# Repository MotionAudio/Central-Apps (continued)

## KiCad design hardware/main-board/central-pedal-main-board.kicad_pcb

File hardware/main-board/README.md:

# Central Pedal main board - rev A

> **Superseded by rev B** (`../main-board-rev-b/`). Do not build rev A as it is: its Pi header frame (pin numbering, mounting holes,
> ribbon slot) was laid out for a mirrored Pi, which was corrected on rev B. Kept for reference only.

270 x 160 mm, 4 layers (signal / GND / 5V1 + VBAT island / signal), 1.6 mm, 1 oz, HASL or ENIG, blue or black.
Stacks behind the Raspberry Pi 4 (2x20 stacking header on the back) with the Raspberry Pi Touch Display 2 in front.
Wiring and pin map: `../../docs/MAIN-BOARD.md`. Full spec: the "Central Pedal Main Board - Design & Manufacturing Spec" doc.

## Ordering (JLCPCB / PCBWay)

Upload from `fab/`:

| File | What |
| --- | --- |
| `central-pedal-main-board-gerbers.zip` | Gerbers + Excellon drills (board edge included) |
| `central-pedal-main-board-bom-jlcpcb.csv` | BOM, with LCSC numbers where a stock part exists |
| `central-pedal-main-board-cpl-jlcpcb.csv` | Pick-and-place (top side only is populated) |
| `central-pedal-main-board-top.pdf` / `-bottom.pdf` | Assembly drawings |
| `central-pedal-main-board-netlist.txt` | Every net and the pins on it, for review |
| `not-fitted.txt` | DNP parts (gain / option jumpers) |
| `drc-report.txt` | KiCad DRC: 0 errors, 0 unconnected; warnings are silkscreen and thermal-relief notes |

Settings to pick: 4 layers, stack-up JLC04161H-7628 (or the fab's standard 4-layer), min track/space 0.15 mm, min
via 0.45 / 0.2 mm (via-in-pad on some ground pads - ask for "filled and capped" vias or accept plain), 5 boards.
Parts without an LCSC number (Neutrik jacks, pots, faders, JST connectors, the push-knobs) can be assembled by the
fab from their global sourcing or soldered by hand; the SMD side is what matters for assembly.

The CPL rotations follow KiCad's convention; the fab's review will rotate polarised parts (diodes, ICs, electrolytics)
to match the Gerbers - confirm them on the assembly preview before paying.

## Regenerating

`design.py` is the whole design (every part, pin and net). On a machine with KiCad 7 and Java:

```
python3 build.py            # place parts, planes, outline -> out/central-pedal-main-board.kicad_pcb
python3 fanout.py --pre     # plane-pad vias before routing
./pipeline.sh               # Freerouting (two passes) + fan-out + stitching
python3 maze.py             # finish any connection the router left open
python3 export.py           # -> out/fab/
```

`central-pedal-main-board.kicad_pcb` / `.kicad_pro` here are the exact routed board the rev A fab files came from.

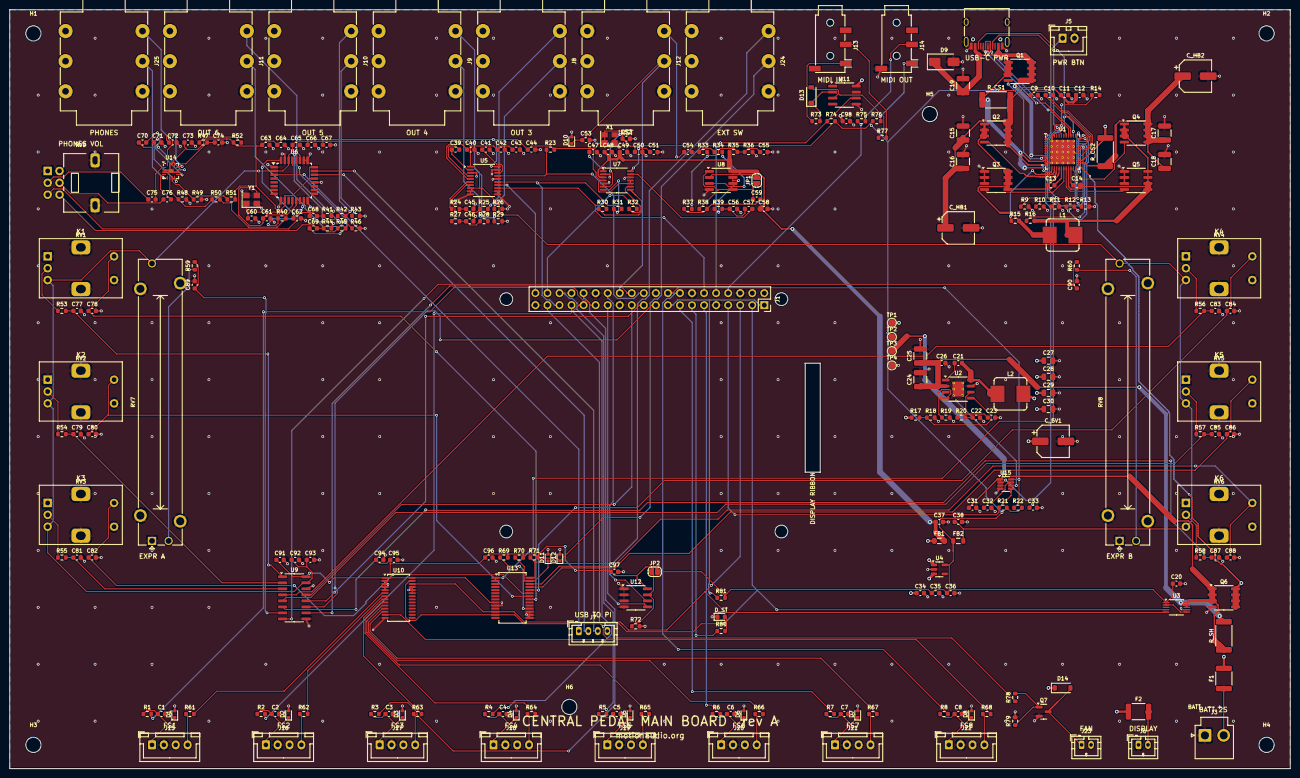
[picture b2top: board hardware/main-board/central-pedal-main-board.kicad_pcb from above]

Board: 4 copper layers, 270.0 x 160.0 mm, 279 parts (0 on the bottom side), 190 nets.

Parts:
C1, C2, C3, C4, C5, C6, C7, C8, C11, C13, C14, C20, C21, C26, C33, C42, C44, C48, C50, C52, C53, C54, C58, C63, C65, C67, C77, C78, C79, C80, C81, C82, C83, C84, C85, C86, C87, C88, C89, C90, C91, C92, C94, C96, C97, C98: 100n; C_0603_1608Metric
C9, C10, C39, C40, C41, C72: 2.2u; C_0603_1608Metric
C12, C31, C34, C35, C51, C57, C70, C71, C73, C75, C76: 1u; C_0603_1608Metric
C15, C16, C17, C18: 22u; C_1210_3225Metric
C19, C24, C25: 10u; C_1210_3225Metric
C22: 4.7n; C_0603_1608Metric
C23: 68p; C_0603_1608Metric
C27, C28, C29, C30: 22u; C_0805_2012Metric
C32: 1.5u; C_0603_1608Metric
C36, C37, C38, C43, C47, C49, C55, C62, C64, C66, C68, C69, C74, C93, C95: 10u; C_0603_1608Metric
C45, C46: 2.2n; C_0603_1608Metric
C56: 1n; C_0603_1608Metric
C59: 100p; C_0603_1608Metric
C60, C61: 22p; C_0603_1608Metric
C_5V1: 100u 10V; CP_Elec_6.3x5.8
C_HB1, C_HB2: 100u 35V; CP_Elec_6.3x5.8
D1, D2, D3, D4, D5, D6, D7, D8, D10, D11, D12: PESD5V0S1UB; D_SOD-523
D9: SMAJ24A; D_SMA
D13, D14: 1N4148W; D_SOD-123
D_ST: GREEN; LED_0603_1608Metric
F1: 7.5A; Fuse_1812_4532Metric
F2: 2A PTC; Fuse_1812_4532Metric
FB1, FB2: FB 600R; L_0805_2012Metric
H1, H2, H3, H4, H5, H6: M3; MountingHole_3.2mm_M3
HPI1, HPI2, HPI3, HPI4: MountingHole_2.7mm
J1: RASPBERRY PI 4; PinSocket_2x20_P2.54mm_Vertical
J2: USB-C; USB_C_Receptacle_HRO_TYPE-C-31-M-12
J3: BATTERY 2S; JST_VH_B2P-VH_1x02_P3.96mm_Vertical
J5: POWER BTN; JST_XH_B2B-XH-A_1x02_P2.50mm_Vertical
J6: DISPLAY 5V; JST_PH_B2B-PH-K_1x02_P2.00mm_Vertical
J7: USB TO PI; JST_PH_B4B-PH-K_1x04_P2.00mm_Vertical
J8, J9, J10, J11, J12, J24, J25: 1/4in TRS; Jack_6.35mm_Neutrik_NMJ6HCD2_Horizontal
J13: MIDI IN; Jack_3.5mm_PJ320D_Horizontal
J14: MIDI OUT; Jack_3.5mm_PJ320D_Horizontal
J15: FOOTSW 1; JST_XH_B4B-XH-A_1x04_P2.50mm_Vertical
J16: FOOTSW 2; JST_XH_B4B-XH-A_1x04_P2.50mm_Vertical
J17: FOOTSW 3; JST_XH_B4B-XH-A_1x04_P2.50mm_Vertical
J18: FOOTSW 4; JST_XH_B4B-XH-A_1x04_P2.50mm_Vertical
J19: FOOTSW 5; JST_XH_B4B-XH-A_1x04_P2.50mm_Vertical
J20: FOOTSW 6; JST_XH_B4B-XH-A_1x04_P2.50mm_Vertical
J21: FOOTSW 7; JST_XH_B4B-XH-A_1x04_P2.50mm_Vertical
J22: FOOTSW 8; JST_XH_B4B-XH-A_1x04_P2.50mm_Vertical
J23: FAN; JST_PH_B2B-PH-K_1x02_P2.00mm_Vertical
JP1: GAIN 0dB; SolderJumper-2_P1.3mm_Open_RoundedPad1.0x1.5mm
JP2: EEPROM WP; SolderJumper-2_P1.3mm_Open_RoundedPad1.0x1.5mm
L1: 10uH 6A; L_Bourns_SRP7028A_7.3x6.6mm
L2: 4.7uH 9A; L_Bourns_SRP7028A_7.3x6.6mm
Q1, Q2, Q3, Q4, Q5: AO4406A; SOIC-8_3.9x4.9mm_P1.27mm
Q6: AO4407A; SOIC-8_3.9x4.9mm_P1.27mm
Q7: AO3400A; SOT-23
R1, R2, R3, R4, R5, R6, R7, R8, R25, R26, R28, R29, R34, R42, R43, R45, R46, R78: 100R; R_0603_1608Metric
R9: 6.2k; R_0603_1608Metric
R10, R11, R12, R13, R14, R18, R37, R40, R69, R70, R71, R72, R79: 10k; R_0603_1608Metric
R15, R16, R75: 10R; R_0603_1608Metric
R17: 53.6k; R_0603_1608Metric
R19: 162k; R_0603_1608Metric
R20: 16.9k; R_0603_1608Metric
R21, R23, R35, R36, R47: 100k; R_0603_1608Metric
R22, R39: 4.7k; R_0603_1608Metric
R24, R27: 470R; R_0603_1608Metric
R30, R31, R32, R76: 33R; R_0603_1608Metric
R33: 1M; R_0603_1608Metric
R38: 30k; R_0603_1608Metric
R41, R44: 47k; R_0603_1608Metric
R48, R49, R50, R51, R52, R77, R81: 0R; R_0603_1608Metric
R53, R54, R55, R56, R57, R58, R59, R60, R80: 1k; R_0603_1608Metric
R61, R62, R63, R64, R65, R66, R67, R68: 330R; R_0603_1608Metric
R73: 220R; R_0603_1608Metric
R74: 2.2k; R_0603_1608Metric
RV1, RV2, RV3, RV4, RV5, RV6: B10K push; RV09_Push_Vertical
RV7, RV8: 10k lin slide; Potentiometer_Bourns_PTA4543_Single_Slide
RV9: A10K dual; Potentiometer_Alps_RK09L_Double_Vertical
R_CS1, R_CS2: 5mR; R_2512_6332Metric
R_SH: 5mR; R_2512_6332Metric
TP1: 5V1; TestPoint_Pad_D1.5mm
TP2: 3V3; TestPoint_Pad_D1.5mm
TP3: VBAT; TestPoint_Pad_D1.5mm
TP4: GND; TestPoint_Pad_D1.5mm
U1: IP2368_BZ; QFN-48-1EP_7x7mm_P0.5mm_EP5.15x5.15mm_ThermalVias
U2: TPS54560DDAR; HSOP-8-1EP_3.9x4.9mm_P1.27mm_EP2.41x3.1mm_ThermalVias
U3: INA226AIDGSR; VSSOP-10_3x3mm_P0.5mm
U4: TLV75533PDBVR; SOT-23-5
U5: PCM5102APWR; TSSOP-20_4.4x6.5mm_P0.65mm
U6: PCM2706CPJTR; TQFP-32_7x7mm_P0.8mm
U7: PCM1808PWR; TSSOP-14_4.4x5mm_P0.65mm
U8: OPA1678IDR; SOIC-8_3.9x4.9mm_P1.27mm
U9: MCP3208-CI/SL; SOIC-16_3.9x9.9mm_P1.27mm
U10: PCA9685PW; TSSOP-28_4.4x9.7mm_P0.65mm
U11: 6N138S; SOIC-8_3.9x4.9mm_P1.27mm
U12: CAT24C32WI-GT3; SOIC-8_3.9x4.9mm_P1.27mm
U13: MCP23017-E/SS; SSOP-28_5.3x10.2mm_P0.65mm
U14: TPA6132A2RTER; Texas_RTE_WQFN-16-1EP_3x3mm_P0.5mm_EP1.2x0.8mm_ThermalVias
U15: LTC2954CTS8-1; TSOT-23-8
X1: 12.288MHz; Oscillator_SMD_Abracon_ASE-4Pin_3.2x2.5mm
Y1: 12MHz; Crystal_SMD_3225-4Pin_3.2x2.5mm

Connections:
3V3: C20.1, C35.1, C36.1, C44.1, C50.1, C52.1, C63.1, C64.1, C73.1, C91.1, C94.1, C95.1, C96.1, C97.1, FB2.1, JP2.2, R14.2, R21.2, R22.2, R23.2, R40.2, R50.2, R51.2, R52.1, R69.2, R70.2, R71.2, R74.2, R76.1, R81.2, TP2.1, U3.1, U3.2, U3.6, U4.5, U5.20, U6.10, U6.21, U6.24, U7.4, U7.10, U7.11, U9.16, U10.1, U10.28, U12.8, U13.9, U14.14, X1.1, X1.4
3V3A: C38.1, C42.1, C43.1, C65.1, C66.1, C67.1, C92.1, C93.1, FB2.2, RV1.3, RV2.3, RV3.3, RV4.3, RV5.3, RV6.3, RV7.3, RV8.3, U5.1, U5.8, U6.2, U6.27, U6.30, U9.15
5V1: C27.1, C28.1, C29.1, C30.1, C34.1, C98.1, C_5V1.1, D14.1, F2.1, FB1.1, J1.2, J1.4, J15.3, J16.3, J17.3, J18.3, J19.3, J20.3, J21.3, J22.3, J23.2, L2.2, R17.1, TP1.1, U4.1, U4.3, U11.8
5VA: C37.1, C48.1, C49.1, C58.1, FB1.2, R35.1, U7.3, U8.8
ADC_BCK: R30.1, U7.8
ADC_CH0: C77.1, R53.2, U9.1
ADC_CH1: C79.1, R54.2, U9.2
ADC_CH2: C81.1, R55.2, U9.3
ADC_CH3: C83.1, R56.2, U9.4
ADC_CH4: C85.1, R57.2, U9.5
ADC_CH5: C87.1, R58.2, U9.6
ADC_CH6: C89.1, R59.2, U9.7
ADC_CH7: C90.1, R60.2, U9.8
ADC_DOUT: R32.1, U7.9
ADC_INL: C57.2, U7.13
ADC_INR: C51.1, U7.14
ADC_LRCK: R31.1, U7.7
ADC_RC: C56.1, C57.1, R39.2
ADC_SCK: U7.6, X1.3
ADC_VREF: C47.1, U7.1
BAT_RAW: F1.1, J3.2
BOOT: C21.1, U2.1
BST1: C13.1, U1.17
BST2: C14.1, U1.22
CAPM: C39.2, U5.4
CAPP: C39.1, U5.2
CC1: J2.A5, U1.41
CC2: J2.B5, U1.38
CHG_LED1: R14.1, U1.43, U13.1
COMP: C23.1, R20.1, U2.6
COMP_C: C22.1, R20.2
CPN: C70.2, U14.9
CPP: C70.1, U14.11
DAC1_L: R24.1, U5.6
DAC1_R: R27.1, U5.7
DAC2_L: C68.1, U6.28
DAC2_R: C69.1, U6.29
DAC_XSMT: J1.22, R23.1, U5.17
DISP_5V: F2.2, J6.2
EEP_WP: JP2.1, R72.1, U12.7
EN_5V: U2.3, U15.6
EXP_RST: R69.1, U13.18
EXT_A: D11.1, J24.T, R70.1, U13.27
EXT_B: D12.1, J24.R, R71.1, U13.28
F1_L: C45.1, R24.2, R25.1
F1_R: C46.1, R27.2, R28.1
FADER1_W: R59.1, RV7.2
FADER2_W: R60.1, RV8.2
FAN_CTL: J1.37, R78.1
FAN_G: Q7.1, R78.2, R79.1
FAN_N: D14.2, J23.1, Q7.3
FB: R17.2, R18.1, U2.5
FS1: C1.1, D1.1, J15.1, R1.1
FS2: C2.1, D2.1, J16.1, R2.1
FS3: C3.1, D3.1, J17.1, R3.1
FS4: C4.1, D4.1, J18.1, R4.1
FS5: C5.1, D5.1, J19.1, R5.1
FS6: C6.1, D6.1, J20.1, R6.1
FS7: C7.1, D7.1, J21.1, R7.1
FS8: C8.1, D8.1, J22.1, R8.1
GND: C1.2, C2.2, C3.2, C4.2, C5.2, C6.2, C7.2, C8.2, C9.2, C10.2, C11.2, C12.2, C15.2, C16.2, C17.2, C18.2, C19.2, C20.2, C22.2, C23.2, C24.2, C25.2, C26.2, C27.2, C28.2, C29.2, C30.2, C31.2, C32.2, C33.2, C34.2, C35.2, C36.2, C37.2, C38.2, C40.2, C41.2, C42.2, C43.2, C44.2, C45.2, C46.2, C47.2, C48.2, C49.2, C50.2, C51.2, C52.2, C53.2, C55.2, C56.2, C58.2, C60.2, C61.2, C62.2, C63.2, C64.2, C65.2, C66.2, C67.2, C71.2, C72.2, C73.2, C74.2, C77.2, C78.2, C79.2, C80.2, C81.2, C82.2, C83.2, C84.2, C85.2, C86.2, C87.2, C88.2, C89.2, C90.2, C91.2, C92.2, C93.2, C94.2, C95.2, C96.2, C97.2, C98.2, C_5V1.2, C_HB1.2, C_HB2.2, D1.2, D2.2, D3.2, D4.2, D5.2, D6.2, D7.2, D8.2, D9.2, D10.2, D11.2, D12.2, D_ST.1, J1.6, J1.9, J1.14, J1.20, J1.25, J1.30, J1.34, J1.39, J2.A1, J2.A12, J2.B1, J2.B12, J2.S1, J3.1, J5.2, J6.1, J7.4, J8.S, J9.S, J10.S, J11.S, J12.S, J12.TN, J14.S, J15.2, J16.2, J17.2, J18.2, J19.2, J20.2, J21.2, J22.2, J24.S, J25.S, Q3.1, Q3.2, Q3.3, Q5.1, Q5.2, Q5.3, Q6.4, Q7.2, R9.2, R10.2, R11.2, R12.2, R13.2, R18.2, R19.2, R26.2, R29.2, R36.2, R41.2, R43.2, R44.2, R46.2, R48.2, R49.2, R72.2, R79.2, RV1.1, RV1.MP, RV1.S2, RV2.1, RV2.MP, RV2.S2, RV3.1, RV3.MP, RV3.S2, RV4.1, RV4.MP, RV4.S2, RV5.1, RV5.MP, RV5.S2, RV6.1, RV6.MP, RV6.S2, RV7.1, RV7.MP, RV8.1, RV8.MP, RV9.1, RV9.4, RV9.MP, TP4.1, U1.11, U1.30, U1.47, U1.49, U2.7, U2.9, U3.7, U4.2, U5.3, U5.9, U5.10, U5.11, U5.12, U5.16, U5.19, U6.1, U6.9, U6.16, U6.20, U6.25, U6.26, U6.31, U7.2, U7.5, U7.12, U8.4, U9.9, U9.14, U10.2, U10.3, U10.4, U10.5, U10.14, U10.23, U10.24, U10.25, U11.5, U12.1, U12.2, U12.3, U12.4, U13.10, U13.15, U13.16, U13.17, U14.2, U14.3, U14.10, U14.15, U14.17, U15.4, X1.2, Y1.2, Y1.4
GND_R3: J8.R, R26.1
GND_R4: J9.R, R29.1
GND_R5: J10.R, R43.1
GND_R6: J11.R, R46.1
GPIO_FS1: J1.29, R1.2
GPIO_FS2: J1.31, R2.2
GPIO_FS3: J1.32, R3.2
GPIO_FS4: J1.33, R4.2
GPIO_FS5: J1.36, R5.2
GPIO_FS6: J1.11, R6.2
GPIO_FS7: J1.15, R7.2
GPIO_FS8: J1.16, R8.2
HB_OUT: C17.1, C18.1, C_HB2.1, Q4.5, Q4.6, Q4.7, Q4.8, R_CS2.1, U1.26
HG1: Q2.4, U1.16
HG2: Q4.4, U1.23
HPIN_L: C75.2, U14.1
HPIN_R: C76.2, U14.4
HPVDD: C72.1, U14.12
HPVOL_L: C75.1, RV9.2
HPVOL_R: C76.1, RV9.5
HPVSS: C71.1, U14.8
HP_EN: C74.1, R47.2, U14.13
HP_G0: R48.1, R50.1, U14.6
HP_G1: R49.1, R51.1, U14.7
HP_L: J25.T, U14.16
HP_R: J25.R, U14.5
I2S_BCK: J1.12, R30.2, U5.13
I2S_DIN: J1.38, R32.2
I2S_DOUT: J1.40, U5.14
I2S_LRCK: J1.35, R31.2, U5.15
ID_SC: J1.28, U12.6
ID_SD: J1.27, U12.5
INST_DET: C53.1, D10.1, J1.26, J12.R
INST_IN: C54.1, J12.T
IN_AC: C54.2, R33.1, R34.1
KCLK1: C78.1, RV1.S1, U13.21
KCLK2: C80.1, RV2.S1, U13.22
KCLK3: C82.1, RV3.S1, U13.23
KCLK4: C84.1, RV4.S1, U13.24
KCLK5: C86.1, RV5.S1, U13.25
KCLK6: C88.1, RV6.S1, U13.26
KNOB1_W: R53.1, RV1.2
KNOB2_W: R54.1, RV2.2
KNOB3_W: R55.1, RV3.2
KNOB4_W: R56.1, RV4.2
KNOB5_W: R57.1, RV5.2
KNOB6_W: R58.1, RV6.2
LDOO: C41.1, U5.18
LED1: R61.2, U10.6
LED2: R62.2, U10.7
LED3: R63.2, U10.8
LED4: R64.2, U10.9
LED5: R65.2, U10.10
LED6: R66.2, U10.11
LED7: R67.2, U10.12
LED8: R68.2, U10.13
LEDK1: J15.4, R61.1
LEDK2: J16.4, R62.1
LEDK3: J17.4, R63.1
LEDK4: J18.4, R64.1
LEDK5: J19.4, R65.1
LEDK6: J20.4, R66.1
LEDK7: J21.4, R67.1
LEDK8: J22.4, R68.1
LED_ST_A: D_ST.2, R80.2
LG1: Q3.4, U1.19
LG2: Q5.4, U1.20
LINE_L: C68.2, R41.1, R42.1, RV9.3
LINE_R: C69.2, R44.1, R45.1, RV9.6
LX1: C13.2, L1.1, Q2.1, Q2.2, Q2.3, Q3.5, Q3.6, Q3.7, Q3.8, R15.2, U1.18
LX2: C14.2, L1.2, Q4.1, Q4.2, Q4.3, Q5.5, Q5.6, Q5.7, Q5.8, R16.2, U1.21
MIDI_A: D13.1, R73.2, U11.2
MIDI_IN_R: J13.R1, R77.2
MIDI_IN_T: J13.T, R73.1
MIDI_K: D13.2, R77.1, U11.3
MIDI_OUT_R: J14.R1, R75.2
MIDI_OUT_T: J14.T, R76.2
MIDI_RX: J1.10, R74.1, U11.6
MIDI_TX: J1.8, R75.1
OUT3: J8.T, R25.2
OUT4: J9.T, R28.2
OUT5: J10.T, R42.2
OUT6: J11.T, R45.2
PB: C33.1, J5.1, U15.2
PCIN: R15.1, U1.15
PCON: R16.1, U1.24
PDT: C32.1, U15.7
PG_5V: R47.1, R52.2
PI_3V3: J1.1, J1.17, R81.1
PRE_A: C59.1, JP1.1, R38.1, U8.1, U8.5
PRE_AN: C59.2, JP1.2, R37.1, R38.2, U8.2
PRE_AP: R34.2, U8.3
PRE_B: R39.1, U8.6, U8.7
PWR_INT: J1.7, R21.1, U15.5
PWR_KILL: J1.18, R22.1, U15.8
ROM_DT: R40.1, U6.15
RT: R19.1, U2.4
R_BATNUM: R9.1, U1.33
R_FCAP: R10.1, U1.34
R_ISET: R12.1, U1.36
R_NTC: R13.1, U1.37
R_VSET: R11.1, U1.35
SCL: J1.5, U3.5, U10.26, U13.12
SDA: J1.3, U3.4, U10.27, U13.13
SPI_CE0: J1.24, U9.10
SPI_MISO: J1.21, U9.12
SPI_MOSI: J1.19, U9.11
SPI_SCLK: J1.23, U9.13
STATUS_LED: J1.13, R80.1
SW: C21.2, L2.1, U2.8
USB2_5V: J7.1, U6.3
USB2_DM: J7.2, U6.22
USB2_DP: J7.3, U6.23
USB_DM: J2.A7, J2.B7, U1.40
USB_DP: J2.A6, J2.B6, U1.39
VBAT: F1.2, Q6.5, Q6.6, Q6.7, Q6.8, R_CS2.2, U1.25, U1.27
VBAT_P: C31.1, Q6.1, Q6.2, Q6.3, R_SH.1, TP3.1, U3.10, U15.1
VBAT_S: C24.1, C25.1, C26.1, R_SH.2, U2.2, U3.8, U3.9
VBIAS: C55.1, R33.2, R35.2, R36.1, R37.2
VBUS: C19.1, D9.1, J2.A4, J2.A9, J2.B4, J2.B9, Q1.5, Q1.6, Q1.7, Q1.8, U1.8
VBUSG: Q1.4, U1.9
VBUS_I: Q1.1, Q1.2, Q1.3, R_CS1.1, U1.10, U1.13
VCC5V: C9.1, U1.29
VCCIO: C10.1, U1.32
VCOM: C62.1, U6.32
VIN_HB: C11.1, C12.1, C15.1, C16.1, C_HB1.1, Q2.5, Q2.6, Q2.7, Q2.8, R_CS1.2, U1.12, U1.14
VNEG: C40.1, U5.5
XTI: C60.1, U6.12, Y1.1
XTO: C61.1, U6.13, Y1.3

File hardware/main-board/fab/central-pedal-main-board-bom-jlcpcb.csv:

Comment,Designator,Footprint,LCSC Part #,Manufacturer Part Number,Quantity,Description
100n,"C1,C2,C3,C4,C5,C6,C7,C8,C11,C13,C14,C20,C21,C26,C33,C42,C44,C48,C50,C52,C53,C54,C58,C63,C65,C67,C77,C78,C79,C80,C81,C82,C83,C84,C85,C86,C87,C88,C89,C90,C91,C92,C94,C96,C97,C98",C_0603_1608Metric,C14663,,46,
2.2u,"C9,C10,C39,C40,C41,C72",C_0603_1608Metric,C23630,,6,
1u,"C12,C31,C34,C35,C51,C57,C70,C71,C73,C75,C76",C_0603_1608Metric,C15849,,11,
22u,"C15,C16,C17,C18",C_1210_3225Metric,,22uF 25V X5R 1210,4,
10u,"C19,C24,C25",C_1210_3225Metric,,10uF 25V X5R 1210,3,
4.7n,C22,C_0603_1608Metric,,,1,
68p,C23,C_0603_1608Metric,,,1,
22u,"C27,C28,C29,C30",C_0805_2012Metric,C45783,22uF 10V X5R 0805,4,
1.5u,C32,C_0603_1608Metric,,1.5uF 16V 0603,1,
10u,"C36,C37,C38,C43,C47,C49,C55,C62,C64,C66,C68,C69,C74,C93,C95",C_0603_1608Metric,C19702,,15,
2.2n,"C45,C46",C_0603_1608Metric,C1593,,2,
1n,C56,C_0603_1608Metric,C1588,,1,
100p,C59,C_0603_1608Metric,C14858,,1,
22p,"C60,C61",C_0603_1608Metric,C1653,,2,
100u 10V,C_5V1,CP_Elec_6.3x5.8,,100uF 10V polymer 6.3x5.8,1,5.1 V bulk
100u 35V,"C_HB1,C_HB2",CP_Elec_6.3x5.8,,100uF 35V polymer 6.3x5.8,2,Charger input bulk
PESD5V0S1UB,"D1,D2,D3,D4,D5,D6,D7,D8,D10,D11,D12",D_SOD-523,,Nexperia PESD5V0S1UB,11,
SMAJ24A,D9,D_SMA,,SMAJ24A TVS,1,USB-C VBUS surge
1N4148W,"D13,D14",D_SOD-123,,1N4148W,2,
GREEN,D_ST,LED_0603_1608Metric,,0603 green LED,1,Status LED (driver running)
7.5A,F1,Fuse_1812_4532Metric,,Littelfuse 0603/1812 7.5A slow,1,Battery fuse
2A PTC,F2,Fuse_1812_4532Metric,,Bourns MF-MSMF200-2,1,Display PTC fuse
FB 600R,"FB1,FB2",L_0805_2012Metric,,BLM21PG600SN1D,2,Ferrite bead 600R@100MHz 1A
RASPBERRY PI 4,J1,PinSocket_2x20_P2.54mm_Vertical,,2x20 female stacking header 2.54 mm,1,Raspberry Pi 4 GPIO (Pi behind the board)
USB-C,J2,USB_C_Receptacle_HRO_TYPE-C-31-M-12,C165948,HRO TYPE-C-31-M-12,1,USB-C charge input
BATTERY 2S,J3,JST_VH_B2P-VH_1x02_P3.96mm_Vertical,,JST B2P-VH,1,2S battery pack (10 A rated)
POWER BTN,J5,JST_XH_B2B-XH-A_1x02_P2.50mm_Vertical,,JST B2B-XH-A,1,Front power button
DISPLAY 5V,J6,JST_PH_B2B-PH-K_1x02_P2.00mm_Vertical,,JST B2B-PH-K-S,1,Touch Display 2 power
USB TO PI,J7,JST_PH_B4B-PH-K_1x04_P2.00mm_Vertical,,JST B4B-PH-K-S,1,Pigtail to a Pi USB-A port
MIDI IN,J13,Jack_3.5mm_PJ320D_Horizontal,,PJ-320D 3.5mm TRRS,1,MIDI IN
MIDI OUT,J14,Jack_3.5mm_PJ320D_Horizontal,,PJ-320D 3.5mm TRRS,1,MIDI OUT
FOOTSW 1,J15,JST_XH_B4B-XH-A_1x04_P2.50mm_Vertical,,JST B4B-XH-A,1,Footswitch 1 + light
FOOTSW 2,J16,JST_XH_B4B-XH-A_1x04_P2.50mm_Vertical,,JST B4B-XH-A,1,Footswitch 2 + light
FOOTSW 3,J17,JST_XH_B4B-XH-A_1x04_P2.50mm_Vertical,,JST B4B-XH-A,1,Footswitch 3 + light
FOOTSW 4,J18,JST_XH_B4B-XH-A_1x04_P2.50mm_Vertical,,JST B4B-XH-A,1,Footswitch 4 + light
FOOTSW 5,J19,JST_XH_B4B-XH-A_1x04_P2.50mm_Vertical,,JST B4B-XH-A,1,Footswitch 5 + light
FOOTSW 6,J20,JST_XH_B4B-XH-A_1x04_P2.50mm_Vertical,,JST B4B-XH-A,1,Footswitch 6 + light
FOOTSW 7,J21,JST_XH_B4B-XH-A_1x04_P2.50mm_Vertical,,JST B4B-XH-A,1,Footswitch 7 + light
FOOTSW 8,J22,JST_XH_B4B-XH-A_1x04_P2.50mm_Vertical,,JST B4B-XH-A,1,Footswitch 8 + light
FAN,J23,JST_PH_B2B-PH-K_1x02_P2.00mm_Vertical,,JST B2B-PH-K-S,1,5 V fan
1/4in TRS,"J8,J9,J10,J11,J12,J24,J25",Jack_6.35mm_Neutrik_NMJ6HCD2_Horizontal,,Neutrik NMJ6HCD2,7,Headphones
GAIN 0dB,JP1,SolderJumper-2_P1.3mm_Open_RoundedPad1.0x1.5mm,,,1,Close = 0 dB (active pickups); open = +12 dB
EEPROM WP,JP2,SolderJumper-2_P1.3mm_Open_RoundedPad1.0x1.5mm,,,1,Close to write-protect the HAT EEPROM
10uH 6A,L1,L_Bourns_SRP7028A_7.3x6.6mm,,Bourns SRP7028A-100M,1,Charger inductor
4.7uH 9A,L2,L_Bourns_SRP7028A_7.3x6.6mm,,Bourns SRP7028A-4R7M,1,5.1 V inductor
AO4406A,"Q1,Q2,Q3,Q4,Q5",SOIC-8_3.9x4.9mm_P1.27mm,,Alpha&Omega AO4406A,5,N-MOSFET 30 V
AO4407A,Q6,SOIC-8_3.9x4.9mm_P1.27mm,,Alpha&Omega AO4407A,1,Reverse-battery protection
AO3400A,Q7,SOT-23,,Alpha&Omega AO3400A,1,Fan switch
100R,"R1,R2,R3,R4,R5,R6,R7,R8,R25,R26,R28,R29,R34,R42,R43,R45,R46,R78",R_0603_1608Metric,C23138,,18,
6.2k,R9,R_0603_1608Metric,,,1,
10k,"R10,R11,R12,R13,R14,R18,R37,R40,R69,R70,R71,R72,R79",R_0603_1608Metric,C25804,,13,
10R,"R15,R16,R75",R_0603_1608Metric,C22859,,3,
53.6k,R17,R_0603_1608Metric,,,1,
162k,R19,R_0603_1608Metric,,,1,
16.9k,R20,R_0603_1608Metric,,,1,
100k,"R21,R23,R35,R36,R47",R_0603_1608Metric,C25741,,5,
4.7k,"R22,R39",R_0603_1608Metric,C23162,,2,
470R,"R24,R27",R_0603_1608Metric,,,2,
33R,"R30,R31,R32,R76",R_0603_1608Metric,C23140,,4,
1M,R33,R_0603_1608Metric,,1M 1% 0603,1,
30k,R38,R_0603_1608Metric,,30k 1% 0603,1,
47k,"R41,R44",R_0603_1608Metric,C25819,,2,
0R,"R48,R49,R52,R77",R_0603_1608Metric,C21189,,4,
1k,"R53,R54,R55,R56,R57,R58,R59,R60,R80",R_0603_1608Metric,C21190,,9,
330R,"R61,R62,R63,R64,R65,R66,R67,R68",R_0603_1608Metric,,330R 0603,8,
220R,R73,R_0603_1608Metric,,220R 0603,1,
2.2k,R74,R_0603_1608Metric,C4190,,1,
B10K push,"RV1,RV2,RV3,RV4,RV5,RV6",RV09_Push_Vertical,,Alpha RV09 / RD901F B10K vertical with push switch,6,Left knob 1
10k lin slide,"RV7,RV8",Potentiometer_Bourns_PTA4543_Single_Slide,,Bourns PTA4543-2015DPB103,2,Left fader
A10K dual,RV9,Potentiometer_Alps_RK09L_Double_Vertical,,Alps RK09L12D0A1S (A10K dual) 9mm vertical,1,Headphone volume
5mR,"R_CS1,R_CS2,R_SH",R_2512_6332Metric,,5 mOhm 1% 2512 sense,3,Input current sense
IP2368_BZ,U1,QFN-48-1EP_7x7mm_P0.5mm_EP5.15x5.15mm_ThermalVias,C5203723,Injoinic IP2368_BZ,1,"2S charger, USB-C PD"
TPS54560DDAR,U2,HSOP-8-1EP_3.9x4.9mm_P1.27mm_EP2.41x3.1mm_ThermalVias,,TI TPS54560DDAR,1,5.1 V / 5 A buck
INA226AIDGSR,U3,VSSOP-10_3x3mm_P0.5mm,,TI INA226AIDGSR,1,"Battery volts / amps, I2C 0x45 (A0 = A1 = VS)"
TLV75533PDBVR,U4,SOT-23-5,,TI TLV75533PDBVR,1,3.3 V 500 mA LDO
PCM5102APWR,U5,TSSOP-20_4.4x6.5mm_P0.65mm,,TI PCM5102APWR,1,"DAC 1 (outputs 3-4), I2S"
PCM2706CPJTR,U6,TQFP-32_7x7mm_P0.8mm,C2651268,TI PCM2706CPJTR,1,"DAC 2 (outputs 5-6 + headphones), USB"
PCM1808PWR,U7,TSSOP-14_4.4x5mm_P0.65mm,,TI PCM1808PWR,1,"Instrument ADC, I2S master"
OPA1678IDR,U8,SOIC-8_3.9x4.9mm_P1.27mm,,TI OPA1678IDR,1,Instrument preamp
MCP3208-CI/SL,U9,SOIC-16_3.9x9.9mm_P1.27mm,,Microchip MCP3208-CI/SL,1,"Knob / fader ADC, SPI"
PCA9685PW,U10,TSSOP-28_4.4x9.7mm_P0.65mm,,NXP PCA9685PW,1,"Footswitch lights, I2C 0x41"
6N138S,U11,SOIC-8_3.9x4.9mm_P1.27mm,,6N138S (SOIC-8),1,MIDI in optocoupler
CAT24C32WI-GT3,U12,SOIC-8_3.9x4.9mm_P1.27mm,,onsemi CAT24C32WI-GT3,1,HAT ID EEPROM
MCP23017-E/SS,U13,SSOP-28_5.3x10.2mm_P0.65mm,,Microchip MCP23017-E/SS,1,"Knob clicks + external footswitches, I2C 0x20"
TPA6132A2RTER,U14,Texas_RTE_WQFN-16-1EP_3x3mm_P0.5mm_EP1.2x0.8mm_ThermalVias,,TI TPA6132A2RTER,1,Headphone amp
LTC2954CTS8-1,U15,TSOT-23-8,,ADI LTC2954CTS8-1#TRMPBF,1,Power button controller
12.288MHz,X1,Oscillator_SMD_Abracon_ASE-4Pin_3.2x2.5mm,,12.288 MHz 3.3 V oscillator 3225,1,ADC master clock
12MHz,Y1,Crystal_SMD_3225-4Pin_3.2x2.5mm,,12 MHz 3225 crystal 18pF,1,USB DAC crystal
